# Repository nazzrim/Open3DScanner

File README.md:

# Open3DScanner

The Open3DScanner is an open source photogrammetry 3D Scanner. Despite its name it does not provide you with the full photogrammetry pipeline.

Instead it enables you to automaticall create sets of photos by using your smartphone camera. These photos need to be processed by your normal photogrammetry pipeline later on.

But by automating the process of capturing the required photos the time you need to spend on creating a 3D scan can significantly decreased.

## Features
- Automatic generation of photosets for photogrammetry
- Support for android and iOS devices
- Adjustable scanning parameters for different granularities of detail
- Integrated LED lights to increase illumination of photos
- Removable backplate and storage area below the baseplate for reduces space requirements
- Adjustable scanner frame for differently sized objects
- Extensive documentation, providing you with build instructions and many additional informations about photogrammetry, the design process, and other open source 3D scanners

## License
Since this repository contains mixed resources (code, documents, images, ...) thera are different licenses which apply to different portions of the repository.

For that reason each subfolder of the root folder contains its own LICENSE.md file which defines the license which applies to the corresponding resources.

But in general code and 3D model resources are licensed under the GPLv3 while media resources (like documents and images) are licensed with the CC-BY-SA 4.0 license.

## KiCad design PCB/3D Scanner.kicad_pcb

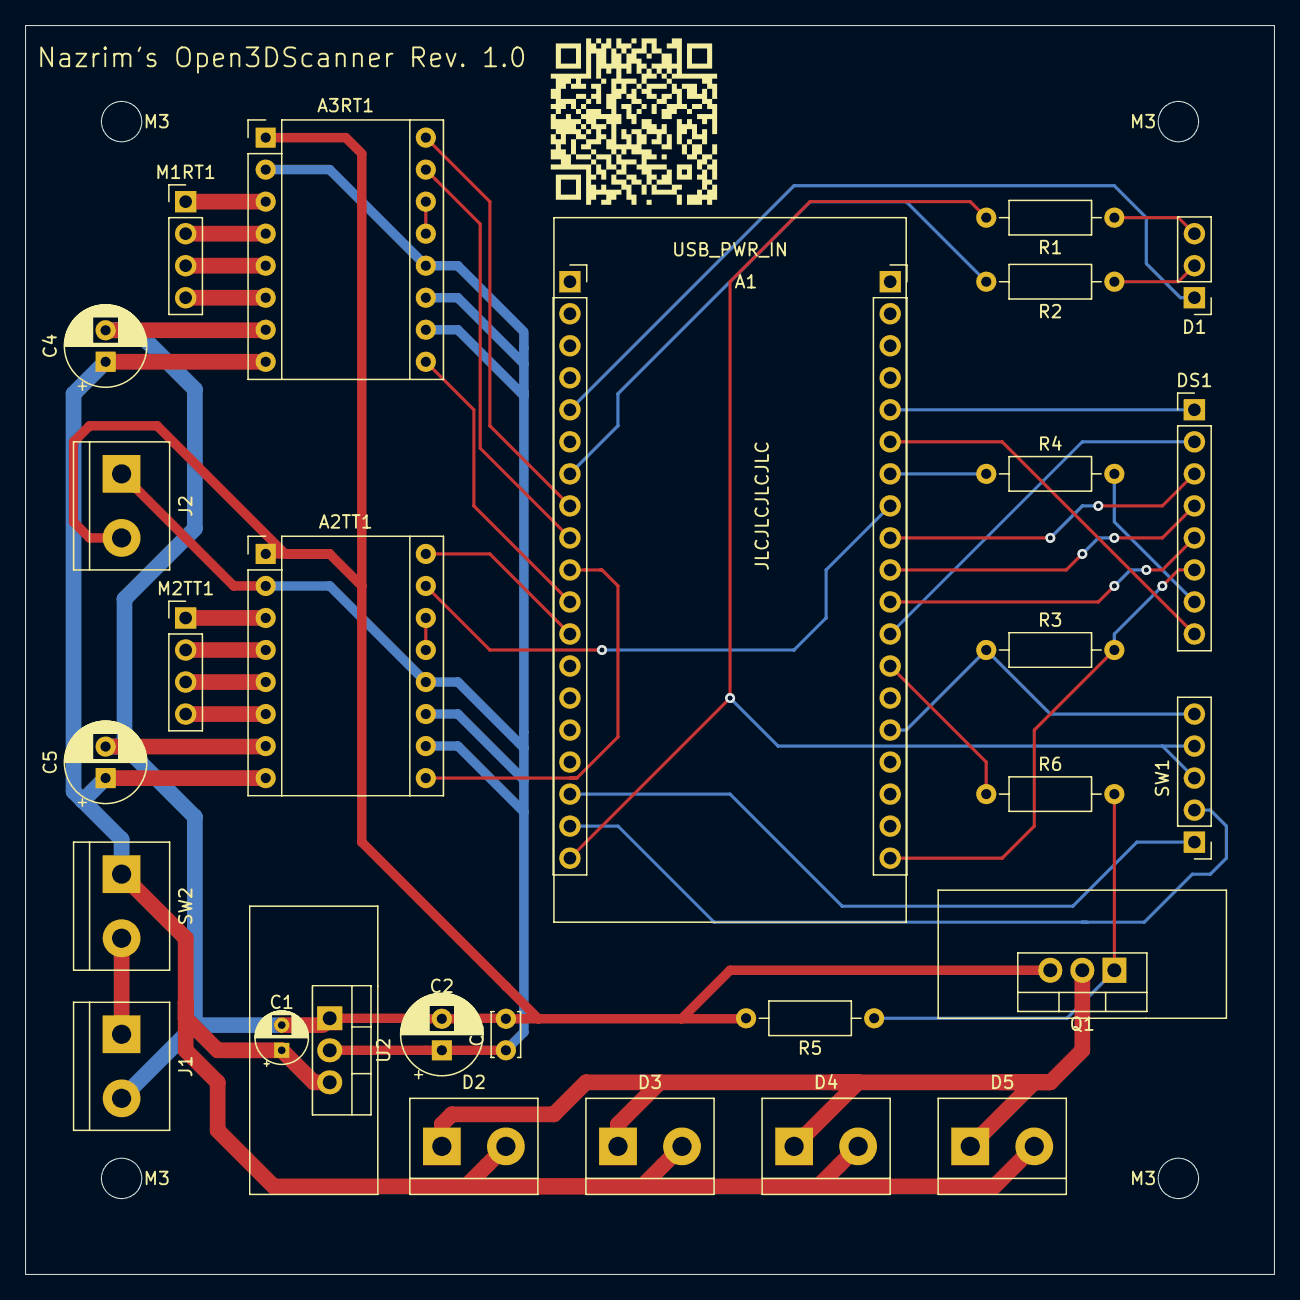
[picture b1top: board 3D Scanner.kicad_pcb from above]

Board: 2 copper layers, 99.1 x 99.1 mm, 33 parts (0 on the bottom side), 40 nets.

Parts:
A1: AZDelivery-ESP32_NodeMCU
A2TT1, A3RT1: Pololu_Breakout_A4988; A4988
C1: 10μ; CP_Radial_D4.0mm_P2.00mm
C2, C4, C5: 100μ; CP_Radial_D6.3mm_P2.50mm
C3: 473n; C_Disc_D3.4mm_W2.1mm_P2.50mm
D1: LED_Dual_AAC; PinHeader_1x03_P2.54mm_Vertical
D2, D3, D4, D5: LED_Series; TerminalBlock_2_P5.08mm
DS1: Nokia5110-Display; PinHeader_1x08_P2.54mm_Vertical
J1: Barrel_Jack; TerminalBlock_2_P5.08mm
J2: Screw_Terminal_01x02; TerminalBlock_2_P5.08mm
M1RT1, M2TT1: Stepper_Motor_bipolar; PinHeader_1x04_P2.54mm_Vertical
M3, M3#2, M3#3, M3#4: M3; MountingHole_3.2mm_M3
Q1: IRLB8721PBF; TO-220-3_Vertical_Cooler
QR*****: QR-Code_MyMiniFactory_Profile
R1, R2, R6: 100; R_Axial_DIN0207_L6.3mm_D2.5mm_P10.16mm_Horizontal
R3, R5: 10k; R_Axial_DIN0207_L6.3mm_D2.5mm_P10.16mm_Horizontal
R4: 330; R_Axial_DIN0207_L6.3mm_D2.5mm_P10.16mm_Horizontal
SW1: Rotary_Encoder_Switch
SW2: SW_SPST; TerminalBlock_2_P5.08mm
U2: LT1086CT-5; TO-220-3_Vertical_Cooler

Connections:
+5V: A2TT1.2, A2TT1.10, A2TT1.11, A2TT1.12, A3RT1.2, A3RT1.10, A3RT1.11, A3RT1.12, C2.1, C3.1, J2.1, U2.2
+12V: A2TT1.8, A3RT1.8, C1.1, C4.1, C5.1, D2.2, D3.2, D4.2, D5.2, SW2.1, U2.3
/GREEN: A1.5, D1.1
/RED: D1.2, R2.1
GND: A2TT1.1, A2TT1.7, A3RT1.1, A3RT1.7, C1.2, C2.2, C3.2, C4.2, C5.2, J1.2, J2.2, Q1.3, R5.2, U2.1
unnamed: A1.7, R2.2
unnamed: A1.8, A3RT1.16
unnamed: A1.9, A3RT1.15
unnamed: A1.10, A2TT1.9
unnamed: A1.11, A3RT1.9
unnamed: A1.12, A2TT1.16
unnamed: A1.17, SW1.A
unnamed: A1.18, SW1.B
unnamed: A1.19, R1.2, SW1.C, SW1.S1
unnamed: A1.24, DS1.1
unnamed: A1.25, DS1.8
unnamed: A1.26, R4.1
unnamed: A1.27, A2TT1.15
unnamed: A1.28, DS1.3
unnamed: A1.29, DS1.4
unnamed: A1.30, DS1.5
unnamed: A1.31, DS1.2
unnamed: A1.32, R6.1
unnamed: A1.34, R3.1, SW1.S2
unnamed: A1.38, DS1.6, R3.2
unnamed: A2TT1.3, M2TT1.1
unnamed: A2TT1.4, M2TT1.2
unnamed: A2TT1.5, M2TT1.3
unnamed: A2TT1.6, M2TT1.4
unnamed: A2TT1.13, A2TT1.14
unnamed: A3RT1.3, M1RT1.1
unnamed: A3RT1.4, M1RT1.2
unnamed: A3RT1.5, M1RT1.3
unnamed: A3RT1.6, M1RT1.4
unnamed: A3RT1.13, A3RT1.14
unnamed: D1.3, R1.1
unnamed: D2.1, D3.1, D4.1, D5.1, Q1.2
unnamed: DS1.7, R4.2
unnamed: J1.1, SW2.2
unnamed: Q1.1, R5.1, R6.2

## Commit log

2019-10-20 Added license
2019-10-20 Added .gitignore
2019-10-20 Adjusted .gitignore
2019-10-20 Added STLs
2019-10-20 Added KiCad Project for the PCB
2019-10-20 Added the manual
2019-10-20 Added the firmware
2019-10-20 Added bitmaps used in the firmware
2019-10-20 Added screenshots of spur gear generator settings
2019-10-20 Edited README
2019-10-23 Splitted license for different resources
    - The firmware is licensed under GPLv3
    - All other artifacts are licensed under CC-BY-SA 4.0
2019-10-23 Added resized logo for README.md
2019-10-23 Improved README.md
2019-10-23 Changes to README.md
2019-10-23 Fixed scan UI issues
2019-10-23 Abortion request screen returns selection dependent value now.
2019-10-25 Increased stand height by 5cm
    Rsolve #3
2019-10-25 Adjust Housing-Plate for Rev. 1.1
2019-10-25 Another adjustment to the license
2019-10-25 Fixed mixed up menu callbacks
    - When leaving the debug menu the light will be turned off
2019-10-25 Leaving scan state will turn off the light now
2019-10-26 Added backplate information to a tip in build instructions.
2019-10-26 Added v1.1 to manual and corrected the license information
2019-10-26 Adjusted manual metadata and title to rev. 1.1
